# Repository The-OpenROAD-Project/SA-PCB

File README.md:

# VLSI-Design-Automation
This repository contains 9 files.

1) Partitioning of ciruits using Fiduccia-Matteyses Algorithm
    -cell.h
    -main1.cpp
    
2) Placement of ciruits using Simulated Annealing Algorithm
    -main2.cpp
    -readFiles.cpp
    -readNets.cpp
    -readScl.cpp
  
3) Routing of circuits using Soukup's and Netmerger Algorithm
    -Netmerger.cpp
    -Soukup.cpp
    -readFile.cpp

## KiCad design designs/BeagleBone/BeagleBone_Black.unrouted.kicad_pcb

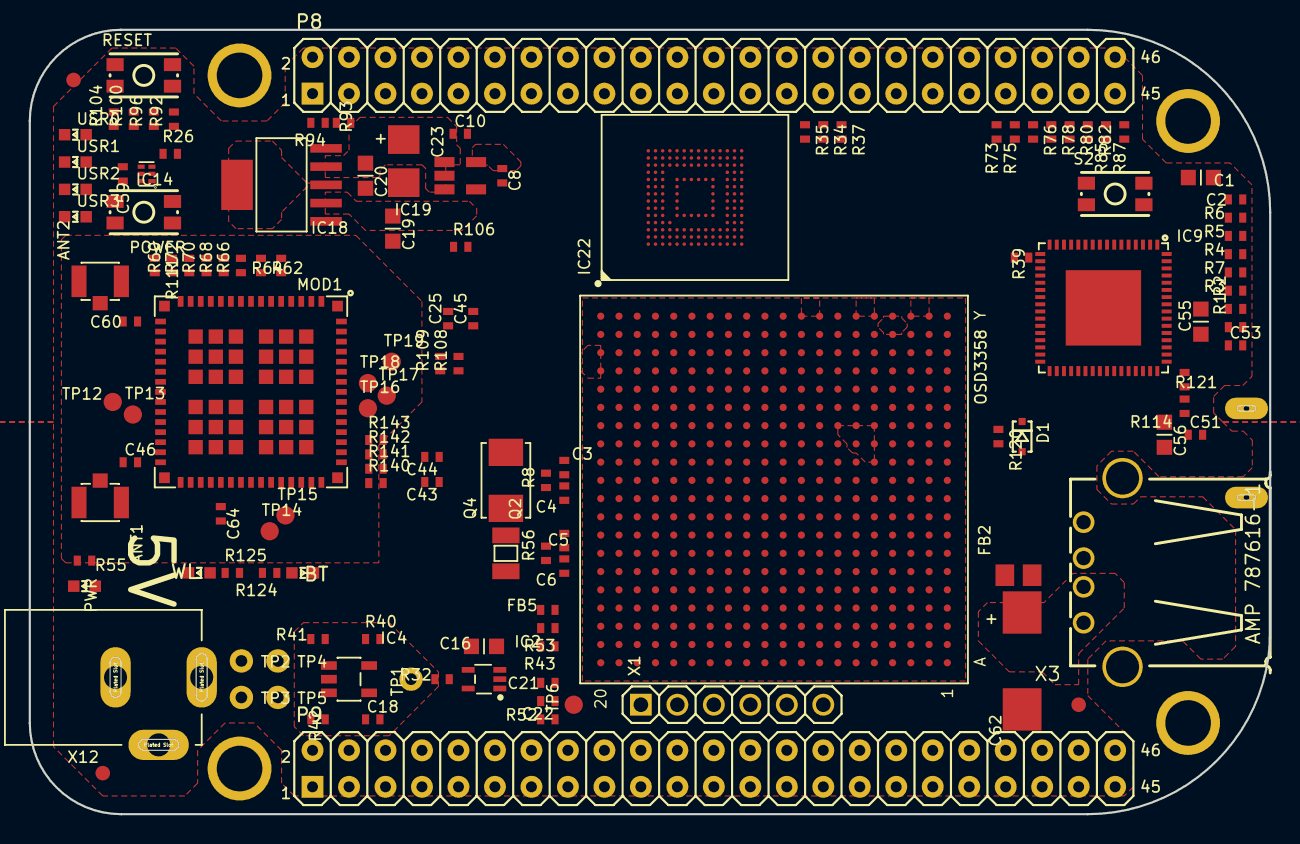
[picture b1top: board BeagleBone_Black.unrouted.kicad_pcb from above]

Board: 6 copper layers, 86.4 x 54.6 mm, 275 parts (0 on the bottom side), 262 nets, no tracks yet.

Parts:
ANT1, ANT2: U.FL-R-SMT-1(10); U.FL-R-SMT-1
BT: LTST-C191TBKT; 0603-LED
C1: 10uF,10V; C0603K
C2, C13, C15, C17, C18, C21, C22, C24, C25, C43, C44, C45, C47, C48, C49, C50, C51, C52, C53, C58, C59, C63, C69: .1uF, 6.3V; C0402K
C3, C4, C5, C6: 18pF, 50V; C0402K
C7: 4.7uF, 6.3V; C0805K
C8, C10: 1uF; C0402K
C9, C12, C14: 2.2uF, 6.3V; C0805K
C11, C23: 47uF DNP; CT3528
C16, C54, C55, C56, C57: 2.2uF, 6.3V; C0603K
C19, C20, C61: 10uF, 6.3V; C0603K
C27, C28, C29, C30, C31, C32, C33, C34, C35, C36, C37, C38, C39, C40, C41, C42: 47pF, 6.3V; C0402K
C46, C60: 10pF; C0402K
C62: 220uF 6.3V; D_7343-31W
C64: 1uF, 6.3V; C0402K
D1: RB751V40,115; SOD323(NXP)REFLOW
D2: STPS140A DNP; DIODE_SMA
D3, D4: STPS140A; DIODE_SMA
D8: BAT54C; SOT23
F1: 1206L025YR; SM-1206
FB1: 220 Ohm 800mA; 0805-RESISTOR
FB2: 2.5k Ohm (BLM18BD252SN1D); 0805-RESISTOR
FB3: 150 Ohm 800mA; 0805-RESISTOR
FB4: 0.1 Ohm, 0805; 0805-RESISTOR
FB5, FB6, FB7: 1k BLM15AG102SN1D; R0402
FUD1, FUD2, FUD3, FUD4, FUD5, FUD6: FIDUCIAL; FIDUCIAL_40MIL
IC1: OSD3358
IC2: SN74LVC1G07DCK; SC70(TI-DCK)
IC3: SN74LVC1G06DCK; SC70(TI-DCK)
IC4: 24LC32AT-I/OT; SOT23-5(MICROCHIP)
IC5: TLVH431 (SOT-23-3); DBZ_R-PDSO-G3
IC6: DNP TLVH431 (SOT-23-3); DBZ_R-PDSO-G3
IC7, IC8: IP4283CZ10-TBR; SOT1176-1(NXP)
IC9: TDA19988BHN/C1,557; SOT804-4(NXP)
IC10, IC11: TXS0108ERGYR; R-PVQFN-N20(TI)
IC12: TPS2051BDGN; MSOP-POWER.PAD-8(TI)
IC13: SN74AUC1G74; SM8-8(TI)
IC14, IC15: TPD4S012DRY; SON-6(TI)-DRY
IC17: SN74LVC2G241DCUR; VSSOP8(TI)
IC18: TL1963ADCQR; SOT-223(DCQ_R-PDSO-G6_TI)
IC19: AP2112K-1.8TRG1 3.3V; SOT23-5
IC22: MICRON_EMMC_153
MGT1, MGT2, MGT3, MGT4: MOUNTING_HOLE
MOD1: WL1835MODGBMOCT; MOC-100(TI)
OSC1: ASDMB-24.576MHZ-LC-T; OSCILLATOR-2.5X2.0-BBB
OSC2: NZ2520SB-32.768KHZ-NSA3534C; NZ2520S
P2: JTAG
P8, P9: TH-2X23
POWER: MINI_PUSHBUTTON
PWR: LTST-C191TBKT; 0603-LED
Q2: 32.768kHz; CRYSTAL_3.2X1.5
Q4: 24 MHz; CRYSTAL_5X3.2MM
R1, R2, R3, R4, R5, R6, R7, R12, R13, R16, R18, R19, R20, R23, R24, R25, R28, R30, R31, R32, R33, R40, R119, R121: 10k, 1%; R0402
R8: 1M, 1%; R0402
R10, R11: 150k; R0402
R14, R26, R27, R29, R35, R36, R37, R38, R39, R54, R114, R122: 0, 1%; R0402
R17: .1, 0805; R0805
R21, R22, R43, R52, R53, R55: 4.75k, 1%; R0402
R34: 22; R0402
R41, R42, R115, R118: 1.5k, 1%; R0402
R44: 499; R0402
R45, R49: DNP; R0402
R46: 10k 1%; R0402
R47: 40.2k 1%; R0402
R48: DNP 499; R0402
R50: DNP 10k 1%; R0402
R51: DNP 40.2k 1%; R0402
R56: DNP 1M, 1%; R0402
R57, R58, R61, R63, R65, R67, R69, R71, R73, R75, R76, R78, R80, R82, R85, R87, R123: 100k, 1%; R0402
R60, R62, R64, R66, R68, R70, R72, R140, R141, R142, R143: 33, 5%; R0402
R86, R126, R127, R128, R129, R130, R131, R134, R135, R136: 33, 5%; R0603
R88: 100, 1%; R0402
R89, R90, R92, R96, R100, R104, R124, R125: 1k; R0402
R91: 0 DNP; R0402
R93: 7.15k; R0402
R94: 4.12k; R0402
R95: 1M; R0402
R97, R108, R109: DNP 1k; R0402
R98, R99, R101, R102, R103, R105: 10k; R0402
R106: 1.5k; R0402
R110: 33; R0402
R111: DNP 10k; R0402
R120: 27k, 1%; R0402
RESET: MINI_PUSHBUTTON
S2: MINI_PUSHBUTTON
T1: MMBT2907; SOT23-BEC
T2: DNP MMBT2907; SOT23-BEC
T3, T4: BSS138W-7-F; SOT-323(DIODES)
TP1, TP2, TP3, TP4, TP5: TESTPAD/W_HOLE_1X1; TESTPAD_W_HOLE_1X1
TP6, TP12, TP13, TP14, TP15, TP16, TP17, TP18, TP19, TP23: PTR1B1,27; B1,27
USR0, USR1, USR2, USR3: LTST-C191TBKT; 0603-LED
WL: LTST-C191TBKT; 0603-LED
X1: TH-1X6
X2: SCHA5B0200
X3: USB_HOST_HORIZONTAL_W_CHASSIS_GND
X4: 10118192-0001LF; 10118192-0001LF(MICRO-USB-B-AMPHENOL-FCI)
X5: 10118241-001RLF; HDMI-TYPE-D-10118241
X12: PJ-102B_POWER_CON

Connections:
3.3V-WIFI: C8.1, C11.+, C24.1, C25.1, C43.1, C64.1, IC10.2, IC11.2, IC19.5, MOD1.38, OSC2.4, R90.1, R98.1, R99.1, R101.1, R102.1, R103.1, R105.1, R111.1
5V_IN: C19.1, D8.3, FB1.2, IC18.2, R95.1
12MHZ: FB6.2, IC9.27
12M_LOOP: IC13.2, IC13.3
32.768KHZ: MOD1.36, OSC2.3, R91.2
AGND: IC1.A6, IC1.A9, IC1.E8, P9.34
AIN0: IC1.B6, P9.39
AIN1: IC1.C7, P9.40
AIN2: IC1.B7, P9.37
AIN3: IC1.A7, P9.38
AIN4: IC1.C8, P9.33
AIN5: IC1.B8, P9.36
AIN6: IC1.A8, P9.35
AIN7: IC1.C9, R21.2, R22.1
ALT.BT.EN: IC10.10, IC11.10, R106.1, R131.1
ALT.BUFF.OE: IC10.15, R126.2
ALT.WL.CLK: IC11.18, R136.2
ALT.WL.CMD: IC11.17, R135.2
ALT.WL.D0: IC10.18, R129.2
ALT.WL.D1: IC10.17, R128.2
ALT.WL.D2: IC10.16, R127.2
ALT.WL.D3: C10.1, C20.1, C23.+, C44.1, C45.1, C61.1, C63.1, IC10.19, IC11.19, IC18.4, IC19.1, IC19.3, MOD1.46, MOD1.47, R93.1, R124.2, R125.2
ALT.WL.EN: IC11.12, R134.2
ALT.WL.IRQ: IC10.20, R130.2
BAT_TEMP: IC1.W1, TP4.P$1
BAT_VOLT: IC1.Y1, TP3.P$1
BT_EN: IC11.4, MOD1.41, R11.1, T4.G
BT_EN.SIP: IC1.K17, R135.1
BT_HCI_CTS: IC11.8, R141.2
BT_HCI_CTS.SIP: IC1.M17, IC11.15, R108.1
BT_HCI_RTS: IC11.6, R140.2
BT_HCI_RTS.SIP: IC1.M18, IC11.13, R109.1
BT_HCI_RX: IC11.1, R143.2
BT_HCI_RX.SIP: IC1.L17, IC11.14
BT_HCI_TX: IC11.7, R142.2
BT_HCI_TX.SIP: IC1.L16, IC11.20
CEC: D1.C, IC9.30, X5.15
CGND: T3.D, WL.K
CLKOUT2: FB7.1, IC11.16, P2.18, P9.41, R14.1
DVI_5V: F1.1, R115.1, R118.1, X5.19
EHRPWM1A: IC1.U14, P9.14
EHRPWM1B: IC1.T14, P9.16
EHRPWM2A: IC1.U10, P8.19
EHRPWM2B: IC1.T10, P8.13
EMMC_RSTN: IC22.K5, R29.1, R33.1
EXT_SWING: IC9.34, R119.1
GND: ANT1.GND1, ANT1.GND2, ANT2.GND1, ANT2.GND2, C1.2, C2.2, C7.2, C8.2, C9.2, C10.2, C11.-, C12.2, C13.2, C14.2, C15.2, C16.2, C17.2, C18.2, C19.2, C20.2, C21.2, C22.2, C23.-, C24.2, C25.2, C27.2, C28.2, C29.2, C30.2, C31.2, C32.2, C33.2, C34.2, C35.2, C36.2, C37.2, C38.2, C39.2, C40.2, C41.2, C42.2, C43.2, C44.2, C45.2, C47.2, C48.2, C49.2, C50.2, C51.2, C52.2, C53.2, C54.2, C55.2, C56.2, C57.2, C58.2, C59.2, C61.2, C62.-, C63.2, C64.2, C69.2, D8.2, IC1.A1, IC1.A18, IC1.E19, IC1.E20, IC1.F8, IC1.F19, IC1.G8, IC1.G9, IC1.G11, IC1.G12, IC1.G19, IC1.H6, IC1.H7, IC1.H8, IC1.H9, IC1.H10, IC1.H12, IC1.H19, IC1.J6, IC1.J7, IC1.J8, IC1.J9, IC1.J10, IC1.J11, IC1.J19, IC1.J20, IC1.K7, IC1.K9, IC1.K10, IC1.K11, IC1.K19, IC1.L10, IC1.L11, IC1.L12, IC1.L13, IC1.L19, IC1.M6, IC1.M7, IC1.M8, IC1.M9, IC1.M10, IC1.M12, IC1.M14, IC1.M19, IC1.N7, IC1.N10, IC1.N11, IC1.N14, IC1.N19, IC1.N20, IC1.P19, IC1.P20, IC1.R19, IC1.R20, IC1.T19, IC1.T20, IC1.U19, IC1.V1, IC1.V18, IC1.V19, IC1.W2, IC1.W3, IC1.W5, IC1.W6, IC1.W7, IC1.W8, IC1.W9, IC1.W10, IC1.W11, IC1.W12, IC1.W13, IC1.W14, IC1.W15, IC1.W16, IC1.W17, IC1.W18, IC1.W19, IC1.W20, IC1.Y7, IC1.Y10, IC1.Y12, IC1.Y15, IC1.Y18, IC2.3, IC3.3, IC4.2, IC7.3, IC7.8, IC8.3, IC8.8, IC9.8, IC9.9, IC9.16, IC9.17, IC9.18, IC9.19, IC9.53, IC9.54, IC9.61, IC9.62, IC9.63, IC9.65, IC10.11, IC10.TP, IC11.11, IC11.TP, IC12.1, IC12.9, IC13.4, IC14.4, IC15.4, IC17.1, IC17.4, IC18.3, IC18.6, IC19.2, IC22.C4, IC22.E7, IC22.G5, IC22.H10, IC22.K8, IC22.N2, IC22.N5, IC22.P4, IC22.P6, MOD1.1, MOD1.7, MOD1.9, MOD1.15, MOD1.16, MOD1.17, MOD1.19, MOD1.20, MOD1.23, MOD1.24, MOD1.28, MOD1.29, MOD1.30, MOD1.31, MOD1.33, MOD1.34, MOD1.35, MOD1.37, MOD1.39, MOD1.44, MOD1.45, MOD1.48, MOD1.49, MOD1.54, MOD1.55, MOD1.59, MOD1.61, MOD1.63, MOD1.64, MOD1.G1, MOD1.G2, MOD1.G3, MOD1.G4, MOD1.G5, MOD1.G6, MOD1.G7, MOD1.G8, MOD1.G9, MOD1.G10, MOD1.G11, MOD1.G12, MOD1.G13, MOD1.G14, MOD1.G15, MOD1.G16, MOD1.G17, MOD1.G18, MOD1.G19, MOD1.G20, MOD1.G21, MOD1.G22, MOD1.G23, MOD1.G24, MOD1.G25, MOD1.G26, MOD1.G27, MOD1.G28, MOD1.G29, MOD1.G30, MOD1.G31, MOD1.G32, MOD1.G33, MOD1.G34, MOD1.G35, MOD1.G36, OSC1.2, OSC2.2, P2.4, P2.8, P2.10, P2.12, P2.16, P2.20, P8.1, P8.2, P9.1, P9.2, P9.43, P9.44, P9.45, P9.46, POWER.1, POWER.2, R10.2, R11.2, R17.1, R19.2, R22.2, R24.1, R27.2, R52.2, R55.1, R57.1, R61.1, R63.1, R65.1, R67.1, R69.1, R71.1, R73.1, R75.1, R85.1, R87.1, R94.2, R95.2, R106.2, R108.2, R109.2, R114.1, R119.2, R123.2, RESET.1, RESET.2, S2.3, S2.4, T3.S, T4.S, TP5.P$1, USR0.K, USR1.K, USR2.K, USR3.K, X1.1, X2.6, X2.GND, X3.4, X4.GND, X5.4, X5.7, X5.10, X5.13, X5.16, X12.OUT
GPIO0_7: P9.42, R36.1, R38.1
GPIO0_26: IC1.T11, P8.14
GPIO0_27: IC1.U12, P8.17
GPIO1_12: IC1.T12, P8.12
GPIO1_13: IC1.R12, P8.11
GPIO1_14: IC1.V13, P8.16
GPIO1_15: IC1.U13, P8.15
GPIO1_16: P9.15, R54.1
GPIO1_16.SIP: IC1.R13, R54.2
GPIO1_17: IC1.V14, P9.23
GPIO1_28: IC1.U18, P9.12
GPIO1_29: IC1.V6, P8.26
GPIO2_1: IC1.V12, P8.18
GPIO3_19: IC1.C13, P9.27
GPIO3_21: IC1.A14, P9.25, R110.2
HDMI.DSCL: IC9.33, R115.2, X5.17
HDMI.DSDA: IC9.32, R118.2, X5.18
HDMICLK_DIS#: IC1.V17, OSC1.1
HDMI_1V8: C50.1, C51.1, C52.1, C53.1, C54.1, C55.1, C56.1, C57.1, FB2.2, IC9.5, IC9.14, IC9.29, IC9.35, IC9.36, IC9.41, IC9.46, IC9.47, IC9.48, IC9.55
HDMI_INT: IC1.U16, IC9.50, R121.2
HPD: IC9.31, X5.1
I2C0_SCL: IC1.C16, IC1.C20, IC4.1, IC9.52, R41.2
I2C0_SDA: IC1.C17, IC1.C19, IC4.3, IC9.51, R42.2
I2C1_SCL: IC1.A16, P9.17
I2C1_SDA: IC1.B16, P9.18
I2C2_SCL: IC1.D17, P9.19
I2C2_SDA: IC1.D18, P9.20
JTAG_EMU0: IC1.C14, P2.13, R43.2
JTAG_EMU1: IC1.B14, P2.14, R53.2
JTAG_TCK: IC1.A12, P2.9, P2.11
JTAG_TDI: IC1.B11, P2.3
JTAG_TDO: IC1.A11, P2.7
JTAG_TMS: IC1.C11, P2.1
JTAG_TRSTN: IC1.B10, P2.2, R52.1
LCD.CLOCK: IC9.4, P8.28, R34.1
LCD.D0.B0--B3: C42.1, IC1.R1, IC9.15, P8.45, R87.2
LCD.D1.B1--B4: C41.1, IC1.R2, IC9.13, P8.46, R85.2
LCD.D2.B2--B5: C40.1, IC1.R3, IC9.12, P8.43, R82.1, R88.1
LCD.D3.B3--B6: C39.1, IC1.R4, IC9.11, P8.44, R80.1
LCD.D4.B4--B7: C38.1, IC1.T1, IC9.10, P8.41, R78.1
LCD.D5.G0--G2: C37.1, IC1.T2, IC9.7, P8.42, R76.1
LCD.D6.G1--G3: C36.1, IC1.T3, IC9.6, P8.39, R75.2
LCD.D7.G2--G4: C35.1, IC1.T4, IC9.3, P8.40, R73.2
LCD.D8.G3--G5: C34.1, IC1.U1, IC9.2, P8.37, R71.2
LCD.D9.G4--G6: C33.1, IC1.U2, IC9.1, P8.38, R69.2
LCD.D10.G5--G7: C32.1, IC1.U3, IC9.64, P8.36, R67.2
LCD.D11.R0--R3: C31.1, IC1.U4, IC9.60, P8.34, R65.2
LCD.D12.R1--R4: C30.1, IC1.V2, IC9.59, P8.35, R63.2
LCD.D13.R2--R5: C29.1, IC1.V3, IC9.58, P8.33, R61.2
LCD.D14.R3--R6: C28.1, IC1.V4, IC9.57, P8.31, R58.1
LCD.D15.R4--R7: C27.1, IC1.T5, IC9.56, P8.32, R57.2
LCD.ENABLE: IC9.20, P8.30, R39.1
LCD.HSYNC: IC9.22, P8.29, R37.1
LCD.VSYNC: IC9.21, P8.27, R35.1
LDO_PGOOD: IC1.B5, IC1.B20
LS_BUF_OE: IC1.L18, R131.2
MCU.LCD.CLK: IC1.V5, R34.2
MCU.LCD.EN: IC1.R6, R39.2
MCU.LCD.HS: IC1.R5, R37.2
MCU.LCD.VS: IC1.U5, R35.2
MMC1_CLK: IC1.U9, IC22.M6, P8.21, R31.1
MMC1_CMD: IC1.V9, IC22.M5, P8.20, R30.1
MMC1_DAT0: IC1.U7, IC22.A3, P8.25, R12.1
MMC1_DAT1: IC1.V7, IC22.A4, P8.24, R13.1
MMC1_DAT2: IC1.R8, IC22.A5, P8.5, R16.1
MMC1_DAT3: IC1.T8, IC22.B2, P8.6, R18.1
MMC1_DAT4: IC1.U8, IC22.B3, P8.23, R20.1
MMC1_DAT5: IC1.V8, IC22.B4, P8.22, R23.1
MMC1_DAT6: IC1.R9, IC22.B5, P8.3, R25.1
MMC1_DAT7: IC1.T9, IC22.B6, P8.4, R28.1
unnamed: OSC2.1, R90.2
unnamed: R88.2, S2.1, S2.2
unnamed: FB5.1, IC1.A15
unnamed: PWR.K, R55.2
unnamed: IC18.1, R89.2, R97.2
unnamed: C4.1, IC1.K20, Q4.1, R8.1
unnamed: C3.1, IC1.M20, Q4.2, R8.2
unnamed: IC1.C6, IC1.D19
unnamed: IC18.5, R93.2, R94.1
unnamed: C3.2, C4.2, IC1.L20
unnamed: C5.2, C6.2, IC1.G20
unnamed: ANT2.SIG, C60.1
unnamed: ANT1.SIG, C46.1
unnamed: C46.2, MOD1.32
unnamed: R100.1, USR1.A
unnamed: R96.1, USR2.A
unnamed: R92.1, USR3.A
unnamed: C60.2, MOD1.18
unnamed: IC1.P17, R27.1
unnamed: IC1.B4, R24.2
unnamed: BT.K, T4.D
unnamed: R125.1, WL.A
unnamed: IC1.D13, R14.2
unnamed: FB7.2, IC1.D14
unnamed: IC1.R14, IC3.2
unnamed: IC3.4, R29.2
unnamed: MOD1.26, TP12.TP
unnamed: R104.1, USR0.A
unnamed: MOD1.27, TP13.TP
unnamed: C5.1, IC1.H20, Q2.P$1, R56.2
unnamed: C6.1, IC1.F20, Q2.P$2, R56.1
unnamed: MOD1.42, TP14.TP
unnamed: MOD1.43, TP15.TP
unnamed: MOD1.56, TP16.TP
unnamed: MOD1.57, TP17.TP
unnamed: OSC1.3, R110.1
unnamed: MOD1.58, TP18.TP
unnamed: MOD1.60, TP19.TP
unnamed: IC1.P15, R26.1
unnamed: C7.1, C69.1, IC22.C2
unnamed: IC1.C18, R36.2
unnamed: IC1.B12, R38.2
unnamed: IC5.2, R44.2, R45.1, T1.B
unnamed: IC5.1, R45.2, R46.2, R47.1
unnamed: IC6.2, R48.2, R49.1, T2.B
unnamed: IC6.1, R49.2, R50.2, R51.1
unnamed: IC4.5, R40.2, TP1.P$1
unnamed: BT.A, R124.1
unnamed: FB6.1, IC13.5
unnamed: MGT1.P$1, MGT2.P$1, MGT3.P$1, MGT4.P$1, R17.2, X2.CGND1, X2.CGND2, X2.CGND3, X2.CGND4, X2.CGND5, X2.CGND6, X3.5, X3.6, X4.CGND1, X4.CGND2, X4.CGND3, X4.CGND4, X4.CGND5, X4.CGND6, X5.CG1, X5.CG2, X5.CG3, X5.CG4
unnamed: MOD1.13, R72.1
unnamed: MOD1.12, R70.1
unnamed: MOD1.11, R68.1
unnamed: MOD1.10, R66.1
unnamed: D1.A, R120.2
unnamed: MOD1.8, R64.1
unnamed: MOD1.6, R62.1
unnamed: MOD1.50, R140.1
unnamed: MOD1.51, R141.1
unnamed: MOD1.52, R142.1
unnamed: MOD1.53, R143.1
unnamed: IC10.14, R86.2
NC3: MOD1.14, R60.1, R111.2
PMIC_INT: IC1.B18, IC1.B19
PMIC_NWAKEUP: IC1.A19, IC1.C5
PMIC_PGOOD: IC1.A20, IC1.B15, IC2.2
PWR_BUT: IC1.D20, P9.9, POWER.3, POWER.4
RX<-TX: IC17.3, X1.5
SD.CD: IC1.C15, P2.19, R7.1, X2.CD
SD.CLK: IC1.G17, R3.1, X2.5
SD.CMD: IC1.G18, R4.1, X2.3
SD.D0: IC1.G16, R2.1, X2.7
SD.D1: IC1.G15, R1.1, X2.8
SD.D2: IC1.F18, R6.1, X2.1
SD.D3: IC1.F17, R5.1, X2.2
SELECT_5V: D2.K, D3.K, D4.K, FB1.1, R97.1, TP23.TP
SLOW_CLK: IC11.5, R91.1
SPI1_CS0: IC1.C12, IC9.25, P9.28
SPI1_D0: IC1.B13, IC9.24, P9.29
SPI1_D1: IC1.D12, P9.30
SPI1_SCLK: IC1.A13, IC9.23, P9.31
SYS_5V: C62.+, D2.A, F1.2, IC1.W4, IC1.Y4, IC12.2, IC12.3, P9.7, P9.8
SYS_RESET#: C16.1, C21.1, IC1.A10, IC2.4, P2.15, P9.10, R32.2, RESET.3, RESET.4
TEST: IC9.49, R114.2
TIMER4: IC1.R7, P8.7
TIMER5: IC1.T6, P8.9
TIMER6: IC1.U6, P8.10
TIMER7: IC1.T7, P8.8
TX0+: IC8.5, IC9.40, X5.9
TX0-: IC8.4, IC9.39, X5.11
TX1+: IC7.2, IC9.43, X5.6
TX1-: IC7.1, IC9.42, X5.8
TX2+: IC7.5, IC9.45, X5.3
TX2-: IC7.4, IC9.44, X5.5
TX->RX: IC17.2, R123.1, X1.4
TXC+: IC8.2, IC9.38, X5.12
TXC-: IC8.1, IC9.37, X5.14
UART0_RST#: IC1.E17, TP6.TP
UART0_RXD: IC1.E15, IC17.6
UART0_TXD: IC1.E16, IC17.5
UART1_RXD: IC1.D16, P9.26
UART1_TXD: IC1.D15, P9.24
UART2_RXD: IC1.A17, P9.22
UART2_TXD: IC1.B17, P9.21
UART4_RXD: IC1.T17, P9.11
UART4_TXD: IC1.U17, P9.13
USB1_DRVVBUS: IC1.F15, IC12.4, R19.1
USB1_OC#: IC1.T16, IC12.5, R122.2
USB1_VBUS: FB4.2, IC1.T18
USB.CLIENT.D+: IC1.N17, IC14.1, X4.D+
USB.CLIENT.D-: IC1.N18, IC14.2, X4.D-
USB.CLIENT.ID: IC1.P16, IC14.3, X4.ID
USB.HOST.D+: IC1.R17, IC15.1, X3.3
USB.HOST.D-: IC1.R18, IC15.2, X3.2
USB_DC: C59.1, D4.A, IC1.Y8, IC1.Y9, IC14.6, R26.2, X4.VBUS
USR0: IC1.V15, R104.2
USR1: IC1.U15, R100.2
USR2: IC1.T15, R96.2
USR3: IC1.V16, R92.2
VBUS.HOST: FB3.2, X3.1
VBUS.OUT: C58.1, FB3.1, FB4.1, IC12.6, IC12.7, IC12.8, IC15.6
VDD_1V8: FB2.1, IC1.D10, IC1.E9, IC1.N16, IC1.R16, IC2.5, IC5.3, IC6.3, R47.2, R51.2, T1.C, T2.C
VDD_3V3A: IC1.N5, IC1.P5, IC1.P6, IC1.P7, R44.1, R46.1, T1.E
VDD_3V3AUX: IC1.Y11, PWR.A
VDD_3V3B: C1.1, C2.1, C9.1, C12.1, C13.1, C14.1, C15.1, C17.1, C18.1, C22.1, C47.1, C48.1, C49.1, IC1.U20, IC1.V20, IC3.5, IC4.4, IC13.6, IC13.7, IC13.8, IC17.7, IC17.8, IC22.C6, IC22.E6, IC22.F5, IC22.J10, IC22.K9, IC22.M4, IC22.N4, IC22.P3, IC22.P5, OSC1.4, P2.5, P9.3, P9.4, R1.2, R2.2, R3.2, R4.2, R5.2, R6.2, R7.2, R12.2, R13.2, R16.2, R18.2, R20.2, R21.1, R23.2, R25.2, R28.2, R30.2, R31.2, R32.1, R33.2, R40.1, R41.1, R42.1, R43.1, R48.1, R50.1, R53.1, R58.2, R76.2, R78.2, R80.2, R82.2, R89.1, R120.1, R121.1, R122.1, T2.E, X2.4
VDD_5V: D3.A, IC1.Y5, IC1.Y6, P9.5, P9.6, X12.IN
VDD_ADC: IC1.A4, IC1.A5, IC1.B9, IC1.D8, P9.32
VIN_BAT: IC1.Y2, IC1.Y3, TP2.P$1
WL_EN: IC11.3, MOD1.40, R10.1, T3.G
WL_EN.SIP: IC1.K18, R136.1
WL_IRQ: IC11.9, R60.2
WL_IRQ.SIP: IC1.H18, R134.1
WL_SDIO_CLK: IC10.6, R64.2, R103.2
WL_SDIO_CLK.SIP: IC1.L15, R126.1
WL_SDIO_CMD: IC10.7, R62.2, R105.2
WL_SDIO_CMD.SIP: IC1.J16, R86.1
WL_SDIO_D0: IC10.1, R66.2, R98.2
WL_SDIO_D0.SIP: IC1.J17, R130.1
WL_SDIO_D1: IC10.3, R68.2, R99.2
WL_SDIO_D1.SIP: IC1.J18, R129.1
WL_SDIO_D2: IC10.4, R70.2, R101.2
WL_SDIO_D2.SIP: IC1.K15, R128.1
WL_SDIO_D3: IC10.5, R72.2, R102.2
WL_SDIO_D3.SIP: IC1.H16, R127.1
XDMA_EVENT_INTRO: FB5.2, IC13.1, P2.17

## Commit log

2019-05-10 init commit
2019-05-10 rm readme
2019-05-10 Delete sa
    no binaries in repo please
2019-05-11 readme
2019-05-11 versioning
2019-05-11 versioning, readme
2019-05-11 submodule add
2019-05-16 rand() -> boos::rand()
2019-05-18 moore terminal bugs fixed
2019-05-20 rotation issue fixed
2019-05-23 routability improvements
2019-06-05 typo
2019-06-05 boundary comp
2019-06-05 cache-rudy
2019-06-05 gitignore
2019-06-06 makefile + reports
2019-06-06 cleanning up stuff
2019-06-08 removed binary from repo
2019-06-08 remove pycache from repo
2019-06-08 remove reports from repo
2019-06-08 moved includes to header file
2019-06-08 broken iterator + pass by reference
2019-06-08 10% faster rudy with static matrices
2019-06-08 removed unused matrix
2019-06-08 clean
2019-06-10 global vars
2019-06-22 mingyu patch
2019-06-22 designs dir
2019-07-18 pre-sri changes
2019-07-18 syntactic edits
2019-07-18 license
2019-07-18 cell_overlap clean
2019-07-18 license & readme
2019-07-18 aesthetic refactor
2019-07-18 taskflow remove
2019-07-18 taskflow rm pt 2
2019-07-18 citations in readme
2019-07-18 requirements.txt
2019-07-19 readme typo
2019-07-19 module dir, make test
2019-07-19 .h -> .hpp
2019-07-19 licensing typo
2019-07-19 e2b module
2019-07-19 rotate flag
2019-07-19 fix compilation bugs
2019-07-19 added hints for refactor
2019-07-22 random_placement typo
2019-07-24 fix some initialization bugs
2019-07-25 bug fixes & perf. optimizations
2019-07-27 new placements
2019-10-12 starting database merge tests
2019-10-17 swig python interp
2019-10-19 dockerfile
2019-10-27 pr flow
2019-10-31 typos
2019-11-01 arg refactor
2019-11-04 refactor hierarchy
2019-11-04 lets try again...
2019-11-04 pre-hanneal changes
2019-11-08 propagate cell & module geometries & netlist up hierarchy
2019-11-12 module netlist bug fix
2019-11-12 ispd2005.py
2019-11-13 greedy placement
2019-11-13 adapt2 cluster and global palcement solution
2019-11-14 cost history vectors
2019-11-18 compatability w/ kicadparser update
2019-11-18 placer wrapper
2019-11-18 bm1 test
2019-11-18 edits
2019-12-11 bsf sol
2019-12-11 bsf sol 2
2019-12-11 fix bsf bug
2019-12-16 tuning api
2019-12-16 reporting
2019-12-17 fix wirelength segfault
2019-12-17 prop
2019-12-18 Update CMakeLists.txt
    simplify swig
2019-12-18 swig/py3
2019-12-18 demo update
2019-12-19 fix pos propagation
2019-12-19 cost & temp callbacks
2019-12-19 remove results
2019-12-23 fix missing py3
2019-12-31 pre ptr fix
2020-01-01 rtree fix
2020-01-01 angle cpp err
2020-01-01 rt api
2020-01-01 forgot rtree api case
2020-01-01 modified lam schedule api
2020-01-01 fix temp issue
2020-01-01 merging...
2020-01-01 refactor some stuff
2020-01-01 nodeit
2020-01-04 layer change bugcheck
2020-01-04 correct pad layer propagation
2020-01-08 placer edits
2020-01-09 demo
2020-01-09 move depreciated modules
2020-01-16 merge
2020-01-16 merging hplace
2020-01-23 hplaceutils
2020-01-23 fix submodule issues
2020-01-30 fix2
2020-02-03 entrapment check draft 1
2020-02-03 finishing up stun test
2020-02-03 hierarchical stun draft
2020-02-03 linreg refactor
2020-02-03 debug messages
2020-02-03 fix some stun issues
2020-02-03 ssamp
2020-02-03 tune eps
2020-02-12 adapt2-cluster video
2020-02-12 adaptec cluster gif
2020-04-08 mirrored file
2020-04-08 logging
2020-04-08 normal -> uniform
2020-04-14 rtree fix 1
2020-04-15 rtree fixes
2020-04-15 logger
2020-04-17 CK experiments
2020-05-03 HPWL fix and some tweaks
2020-05-03 remove greedy hardcode
